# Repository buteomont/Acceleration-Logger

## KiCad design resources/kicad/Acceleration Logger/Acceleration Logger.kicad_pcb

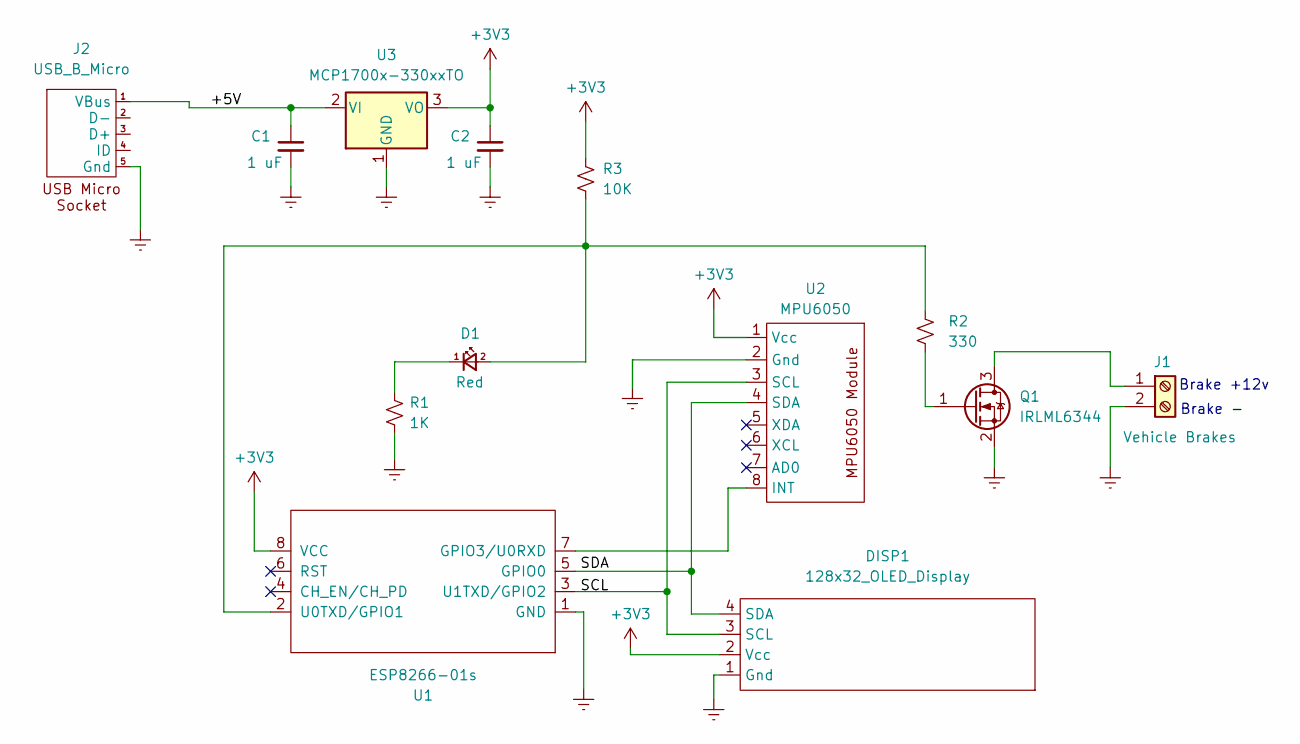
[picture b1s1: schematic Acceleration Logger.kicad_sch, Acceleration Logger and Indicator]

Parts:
C1, C2: 1 uF; C_0805_2012Metric_Pad1.18x1.45mm_HandSolder
D1: Red; LED_D5.0mm
DISP1: 128x32_OLED_Display; OLED_0.91_128x32
J1: Vehicle Brakes; KF350 2 Pin Terminal Block
J2: USB_B_Micro; USB Micro Breakout Board
Q1: IRLML6344; SOT-23
R1: 1K; R_0805_2012Metric_Pad1.20x1.40mm_HandSolder
R2: 330; R_0805_2012Metric_Pad1.20x1.40mm_HandSolder
R3: 10K; R_0805_2012Metric_Pad1.20x1.40mm_HandSolder
U1: ESP8266-01s
U2: MPU6050; MPU6050_Accelerometer_Module
U3: MCP1700x-330xxTO; TO-92_Inline

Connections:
+3V3: C2.1, DISP1.2 (Vcc), R3.1, U1.8 (VCC), U2.1 (Vcc), U3.3 (VO)
/+5V: C1.1, J2.1 (VBus), U3.2 (VI)
/SDA: DISP1.4 (SDA), U1.5 (GPIO0), U2.4 (SDA)
Earth: C1.2, C2.2, DISP1.1 (Gnd), J1.2, J2.5 (Gnd), Q1.2 (S), R1.2, U1.1 (GND), U2.2 (Gnd), U3.1 (GND)
unnamed: D1.2 (A), R2.1, R3.2, U1.2 (U0TXD/GPIO1)
unnamed: D1.1 (K), R1.1
unnamed: DISP1.3 (SCL), U1.3 (U1TXD/GPIO2), U2.3 (SCL)
unnamed: J1.1, Q1.3 (D)
unnamed: Q1.1 (G), R2.2
unnamed: U1.7 (GPIO3/U0RXD), U2.8 (INT)

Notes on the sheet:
Brake -
Brake +12v

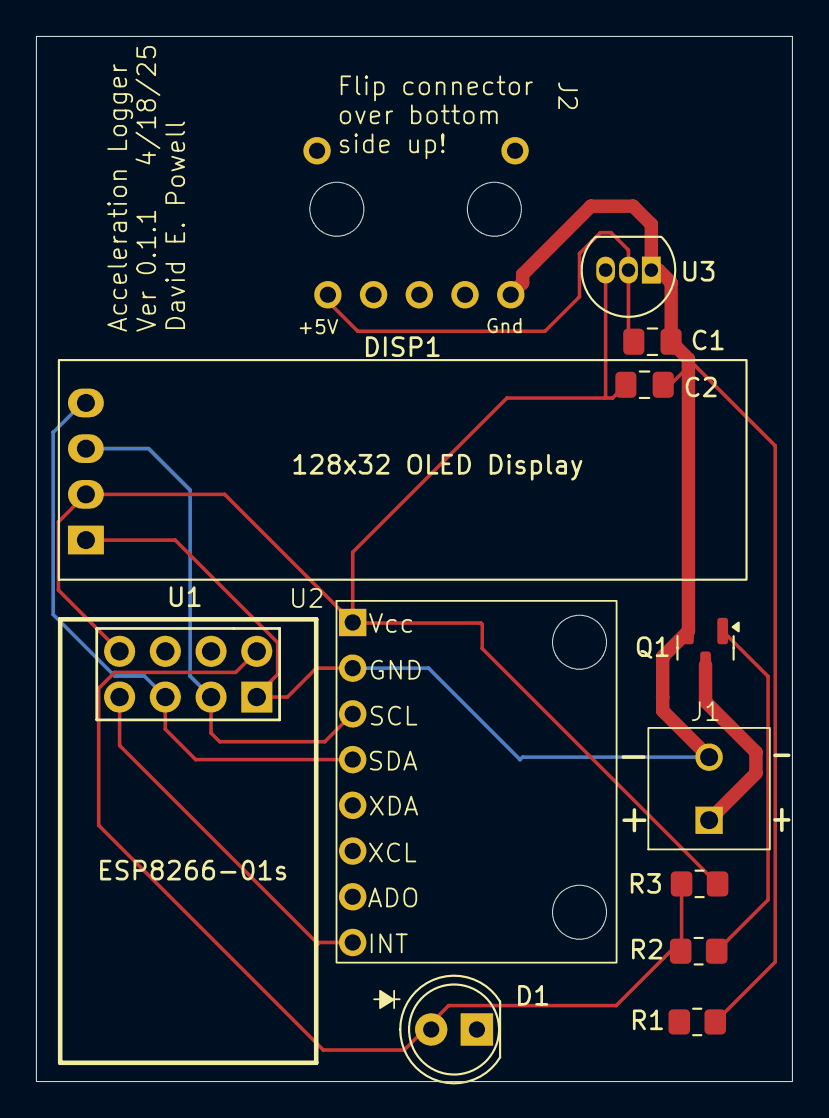
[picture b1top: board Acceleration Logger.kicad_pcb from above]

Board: 2 copper layers, 42.0 x 58.1 mm, 13 parts (1 on the bottom side), 10 nets.

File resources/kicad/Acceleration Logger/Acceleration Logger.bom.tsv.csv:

Ref		Value
	C1,C2	1 uF
	D1		Red
DISP1	128x32_OLED_Display
J1		Vehicle Brakes
J2		USB_B_Micro
	Q1		IRLML6344
	R1		1K
	R2		330
	R3		10K
U1		ESP8266-01s
U2		MPU6050
U3		MCP1700x-330xxTO

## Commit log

2025-03-28 Many updates
2025-03-30 Cleaned up the web page. Added an override function to show().
2025-04-04 Minor fixes all around
2025-04-17 Board updates
2025-04-22 Added "set level" feature. Changed LED to T1-3/4 size
